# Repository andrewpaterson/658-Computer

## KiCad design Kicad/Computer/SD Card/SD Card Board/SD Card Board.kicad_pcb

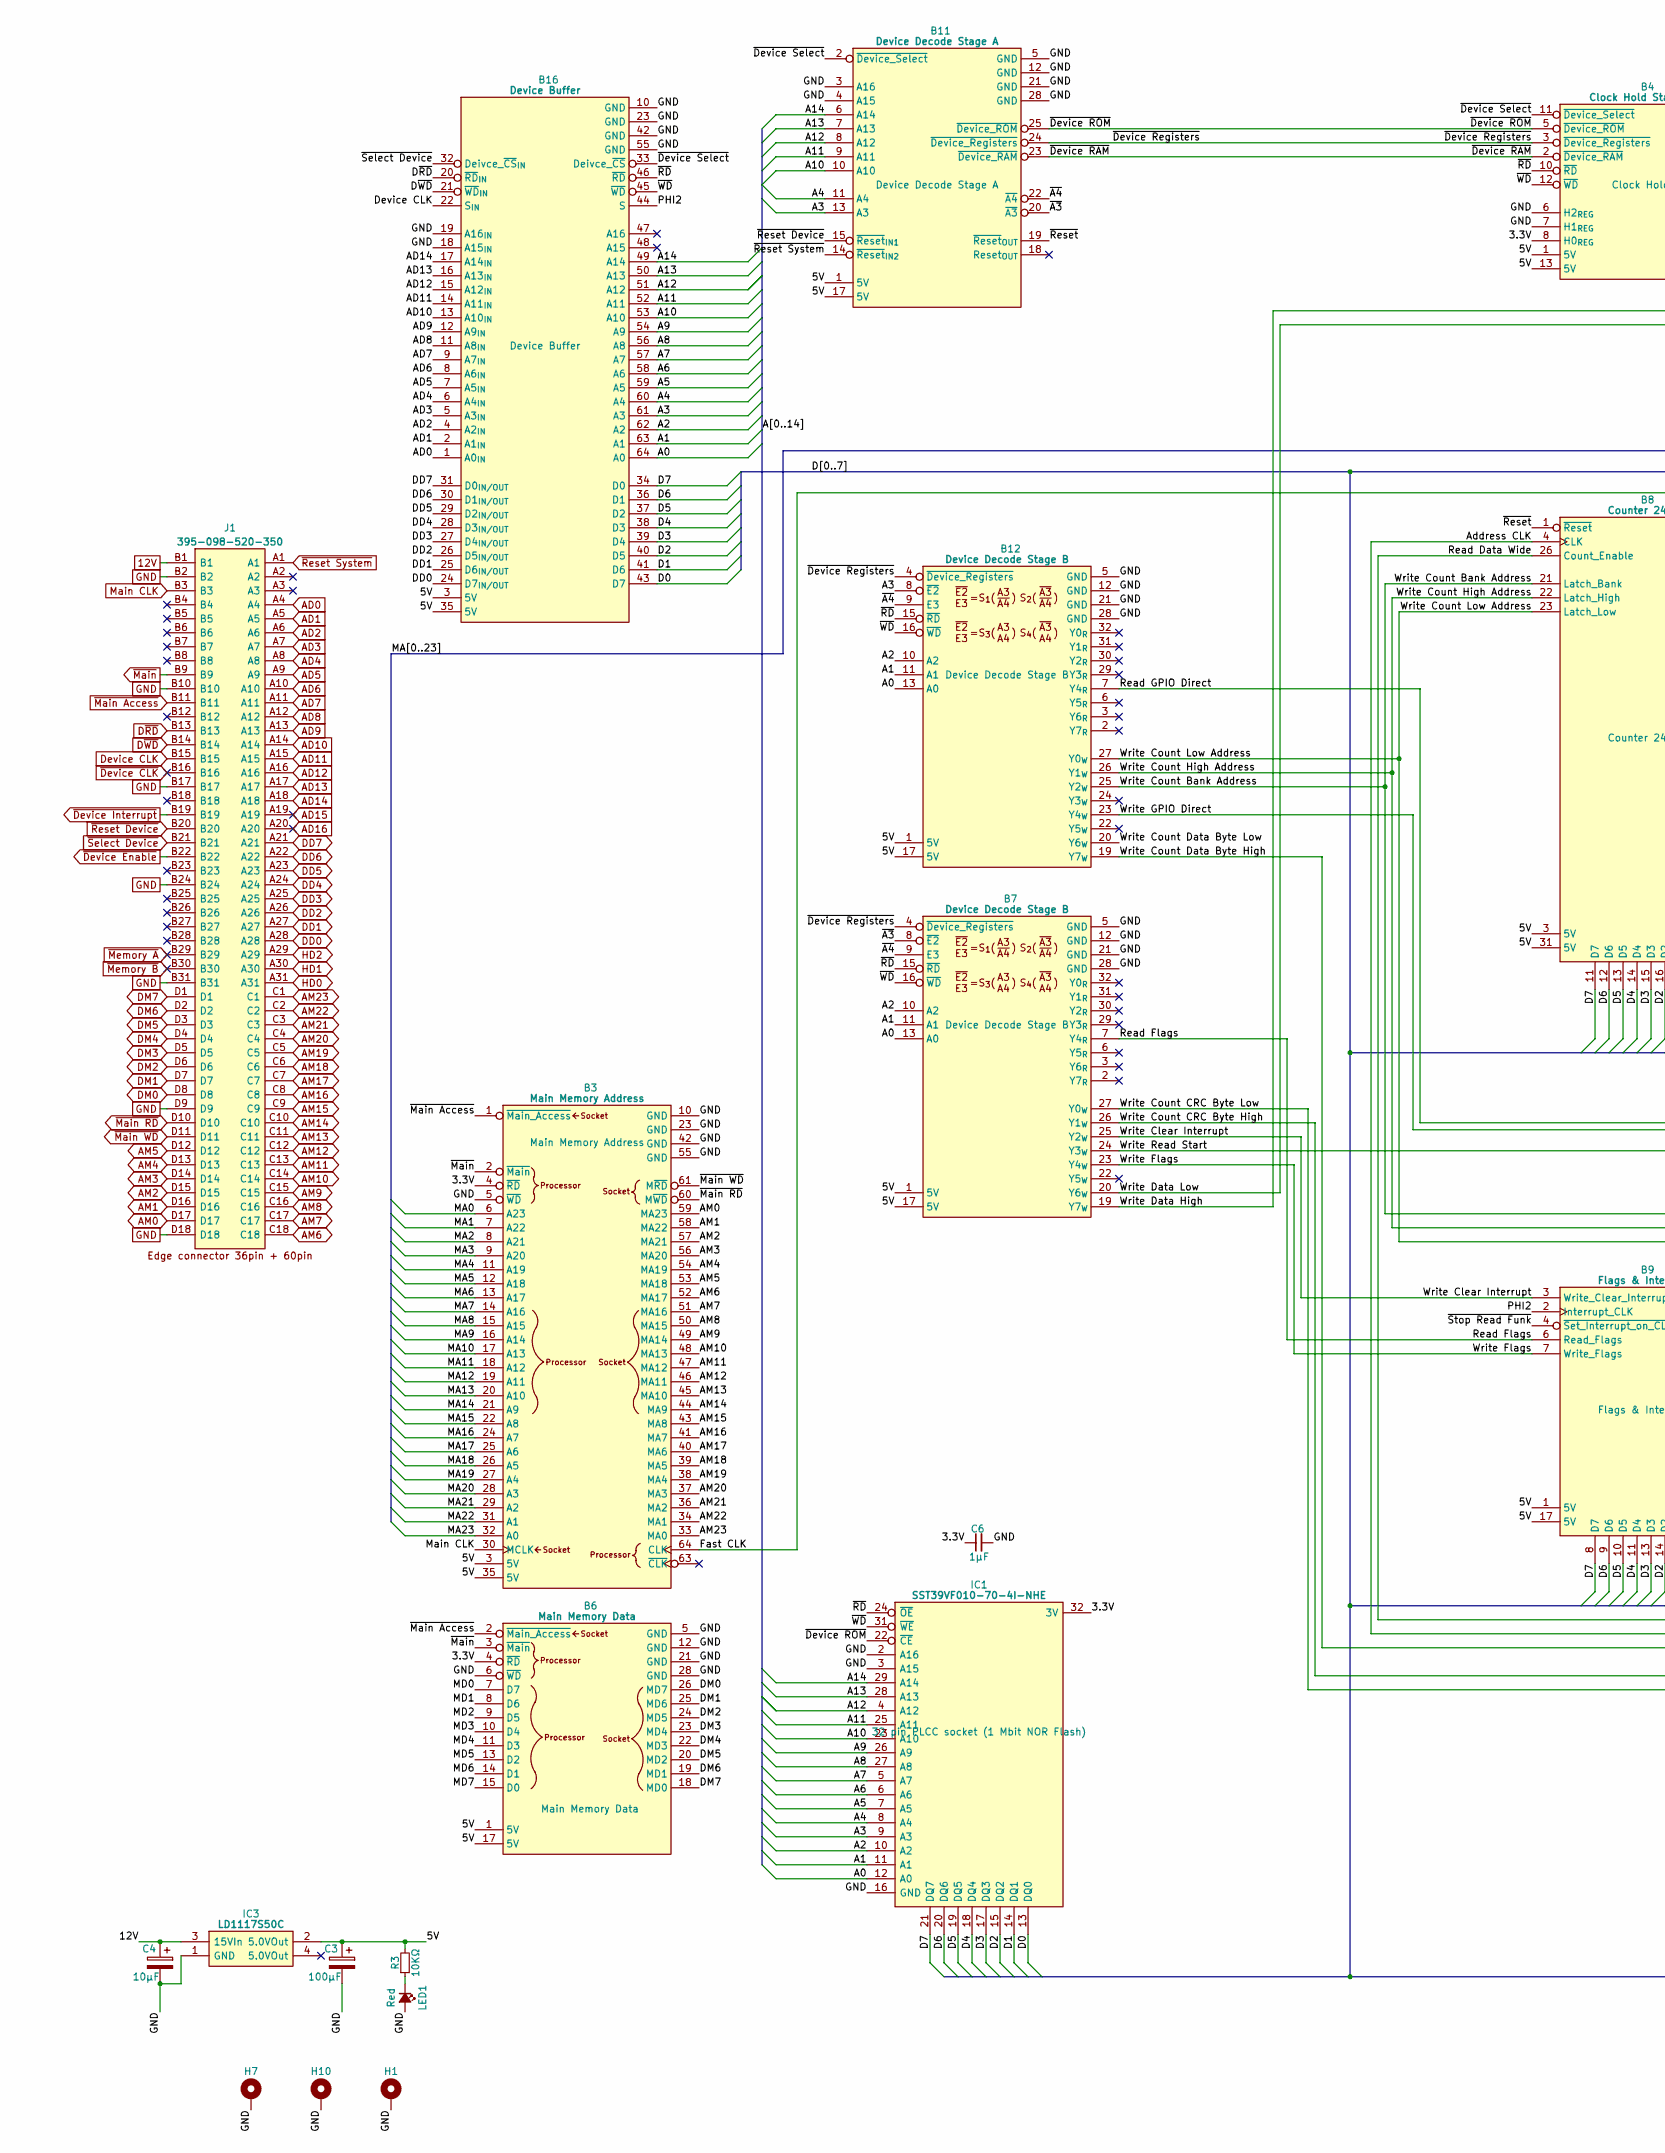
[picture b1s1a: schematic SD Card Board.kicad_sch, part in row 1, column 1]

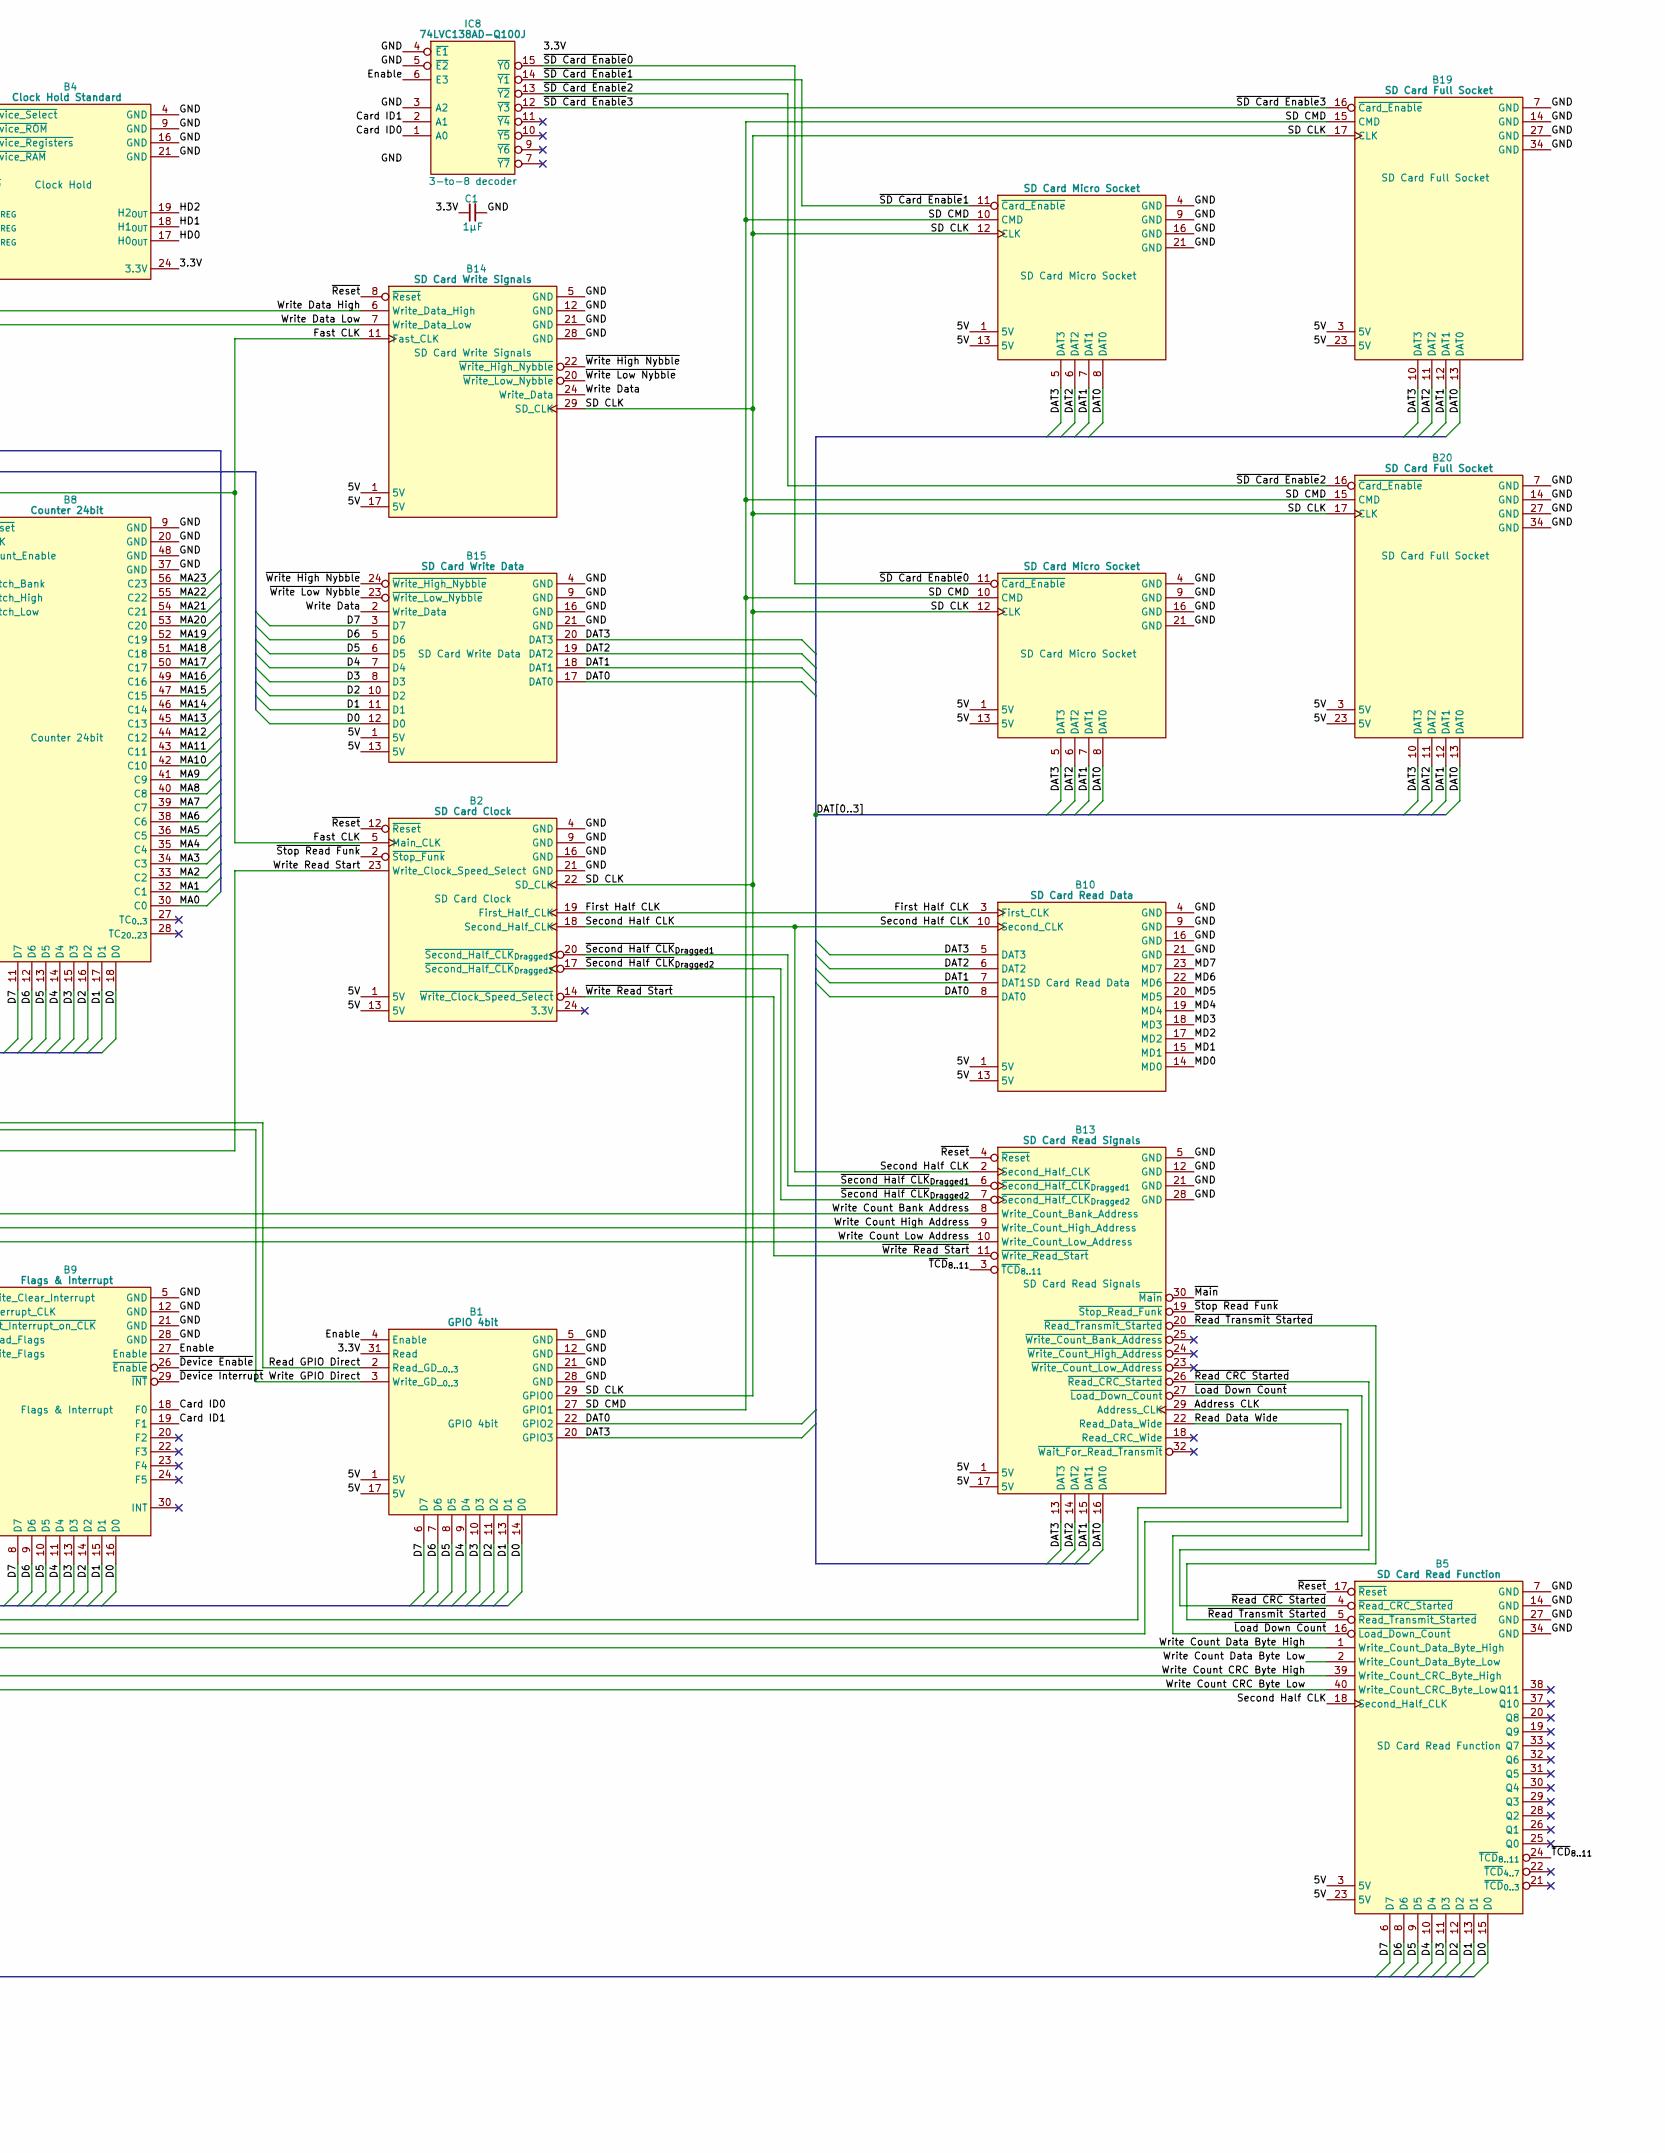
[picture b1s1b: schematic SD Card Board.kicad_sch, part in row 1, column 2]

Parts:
B1: GPIO 4bit; HCP65_GPIO_4bit
B2: SD Card Clock; HCP65_SD_Card_Clock
B3: Main Memory Address; HCP65_Main_Memory_Address
B4: Clock Hold Standard; HCP65_Clock_Hold_Standard
B5: SD Card Read Function; HCP65_SD_Card_Read_Function
B6: Main Memory Data; HCP65_Main_Memory_Data
B7, B12: Device Decode Stage B; HCP65_Device_Decode_Stage_B
B8: Counter 24bit; HCP65_Counter_24bit
B9: Flags & Interrupt; HCP65_Flags_Interrupt
B10: SD Card Read Data; HCP65_SD_Card_Read_Data
B11: Device Decode Stage A; HCP65_Device_Decode_Stage_A
B13: SD Card Read Signals; HCP65_SD_Card_Read_Signals
B14: SD Card Write Signals; HCP65_SD_Card_Write_Signals
B15: SD Card Write Data; HCP65_SD_Card_Write_Data
B16: Device Buffer; HCP65_Device_Buffer
B17, B18: SD Card Micro Socket; HCP65_SD_Card_Micro_Socket
B19, B20: SD Card Full Socket; HCP65_SD_Card_Full_Socket
C1, C6: 1μF; C_0805
C3: 100μF; CP_Radial_D4.0mm_P2.00mm
C4: 10μF; CP_Radial_D4.0mm_P2.00mm
H1, H7, H10: MountingHole_Pad; HCP65_MountingHole_M3_
IC1: SST39VF010-70-4I-NHE; 5408803224008; Manufacturer_Part_Number SST39VF010-70-4I-NHE
IC3: LD1117S50C; LD1117S33C; Manufacturer_Part_Number LD1117S50C
IC8: 74LVC138AD-Q100J; SOIC127P600X175-16N; Mouser Part Number 771-74LVC138ADQ100J
J1: 395-098-520-350; 98pin Edge Connector; Manufacturer_Part_Number 395-098-520-350; Mouser Part Number 587-395-098-520-350
LED1: Red; LED_D5.0mm
R3: 10KΩ; R_0805

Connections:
12V: C4.1, IC3.3 (15VIn), J1.B1
/3.3V: B1.31 (Read), B3.4 (~RD), B4.8 (H0_{REG}), B4.24 (3.3V), B6.4 (~RD), C1.1, C6.1, IC1.32 (3V), IC8.16 (3V)
/5V: B1.1 (5V), B1.17 (5V), B2.1 (5V), B2.13 (5V), B3.3 (5V), B3.35 (5V), B4.1 (5V), B4.13 (5V), B5.3 (5V), B5.23 (5V), B6.1 (5V), B6.17 (5V), B7.1 (5V), B7.17 (5V), B8.3 (5V), B8.31 (5V), B9.1 (5V), B9.17 (5V), B10.1 (5V), B10.13 (5V), B11.1 (5V), B11.17 (5V), B12.1 (5V), B12.17 (5V), B13.1 (5V), B13.17 (5V), B14.1 (5V), B14.17 (5V), B15.1 (5V), B15.13 (5V), B16.3 (5V), B16.35 (5V), B17.1 (5V), B17.13 (5V), B18.1 (5V), B18.13 (5V), B19.3 (5V), B19.23 (5V), B20.3 (5V), B20.23 (5V), C3.1, IC3.2 (5.0VOut), R3.2
/A0: B7.13 (A0), B12.13 (A0), B16.64 (A0), IC1.12 (A0)
/A1: B7.11 (A1), B12.11 (A1), B16.63 (A1), IC1.11 (A1)
/A2: B7.10 (A2), B12.10 (A2), B16.62 (A2), IC1.10 (A2)
/A3: B11.13 (A3), B12.8 (~E2), B16.61 (A3), IC1.9 (A3)
/A4: B11.11 (A4), B16.60 (A4), IC1.8 (A4)
/A5: B16.59 (A5), IC1.7 (A5)
/A6: B16.58 (A6), IC1.6 (A6)
/A7: B16.57 (A7), IC1.5 (A7)
/A8: B16.56 (A8), IC1.27 (A8)
/A9: B16.54 (A9), IC1.26 (A9)
/A10: B11.10 (A10), B16.53 (A10), IC1.23 (A10)
/A11: B11.9 (A11), B16.52 (A11), IC1.25 (A11)
/A12: B11.8 (A12), B16.51 (A12), IC1.4 (A12)
/A13: B11.7 (A13), B16.50 (A13), IC1.28 (A13)
/A14: B11.6 (A14), B16.49 (A14), IC1.29 (A14)
/Address CLK: B8.4 (CLK), B13.29 (Address_CLK)
/Card ID0: B9.18 (F0), IC8.1 (A0)
/Card ID1: B9.19 (F1), IC8.2 (A1)
/D0: B1.14 (D0), B5.15 (D0), B8.18 (D0), B9.16 (D0), B15.12 (D0), B16.43 (D7), IC1.13 (DQ0)
/D1: B1.13 (D1), B5.13 (D1), B8.17 (D1), B9.15 (D1), B15.11 (D1), B16.41 (D6), IC1.14 (DQ1)
/D2: B1.11 (D2), B5.12 (D2), B8.16 (D2), B9.14 (D2), B15.10 (D2), B16.40 (D5), IC1.15 (DQ2)
/D3: B1.10 (D3), B5.11 (D3), B8.15 (D3), B9.13 (D3), B15.8 (D3), B16.39 (D4), IC1.17 (DQ3)
/D4: B1.9 (D4), B5.10 (D4), B8.14 (D4), B9.11 (D4), B15.7 (D4), B16.38 (D3), IC1.18 (DQ4)
/D5: B1.8 (D5), B5.9 (D5), B8.13 (D5), B9.10 (D5), B15.6 (D5), B16.37 (D2), IC1.19 (DQ5)
/D6: B1.7 (D6), B5.8 (D6), B8.12 (D6), B9.9 (D6), B15.5 (D6), B16.36 (D1), IC1.20 (DQ6)
/D7: B1.6 (D7), B5.6 (D7), B8.11 (D7), B9.8 (D7), B15.3 (D7), B16.34 (D0), IC1.21 (DQ7)
/DAT0: B1.22 (GPIO2), B10.8 (DAT0), B13.16 (DAT0), B15.17 (DAT0), B17.8 (DAT0), B18.8 (DAT0), B19.13 (DAT0), B20.13 (DAT0)
/DAT1: B10.7 (DAT1), B13.15 (DAT1), B15.18 (DAT1), B17.7 (DAT1), B18.7 (DAT1), B19.12 (DAT1), B20.12 (DAT1)
/DAT2: B10.6 (DAT2), B13.14 (DAT2), B15.19 (DAT2), B17.6 (DAT2), B18.6 (DAT2), B19.11 (DAT2), B20.11 (DAT2)
/DAT3: B1.20 (GPIO3), B10.5 (DAT3), B13.13 (DAT3), B15.20 (DAT3), B17.5 (DAT3), B18.5 (DAT3), B19.10 (DAT3), B20.10 (DAT3)
/Enable: B1.4 (Enable), B9.27 (Enable), IC8.6 (E3)
/Fast CLK: B2.5 (Main_CLK), B3.64 (CLK), B14.11 (Fast_CLK)
/First Half CLK: B2.19 (First_Half_CLK), B10.3 (First_CLK)
/MA0: B3.6 (A23), B8.30 (C0)
/MA1: B3.7 (A22), B8.32 (C1)
/MA2: B3.8 (A21), B8.33 (C2)
/MA3: B3.9 (A20), B8.34 (C3)
/MA4: B3.11 (A19), B8.35 (C4)
/MA5: B3.12 (A18), B8.36 (C5)
/MA6: B3.13 (A17), B8.38 (C6)
/MA7: B3.14 (A16), B8.39 (C7)
/MA8: B3.15 (A15), B8.40 (C8)
/MA9: B3.16 (A14), B8.41 (C9)
/MA10: B3.17 (A13), B8.42 (C10)
/MA11: B3.18 (A12), B8.43 (C11)
/MA12: B3.19 (A11), B8.44 (C12)
/MA13: B3.20 (A10), B8.45 (C13)
/MA14: B3.21 (A9), B8.46 (C14)
/MA15: B3.22 (A8), B8.47 (C15)
/MA16: B3.24 (A7), B8.49 (C16)
/MA17: B3.25 (A6), B8.50 (C17)
/MA18: B3.26 (A5), B8.51 (C18)
/MA19: B3.27 (A4), B8.52 (C19)
/MA20: B3.28 (A3), B8.53 (C20)
/MA21: B3.29 (A2), B8.54 (C21)
/MA22: B3.31 (A1), B8.55 (C22)
/MA23: B3.32 (A0), B8.56 (C23)
/MD0: B6.7 (D7), B10.14 (MD0)
/MD1: B6.8 (D6), B10.15 (MD1)
/MD2: B6.9 (D5), B10.17 (MD2)
/MD3: B6.10 (D4), B10.18 (MD3)
/MD4: B6.11 (D3), B10.19 (MD4)
/MD5: B6.13 (D2), B10.20 (MD5)
/MD6: B6.14 (D1), B10.22 (MD6)
/MD7: B6.15 (D0), B10.23 (MD7)
/PHI2: B9.2 (Interrupt_CLK), B16.44 (S)
/Read Data Wide: B8.26 (Count_Enable), B13.22 (Read_Data_Wide)
/Read Flags: B7.7 (Y4_{R}), B9.6 (Read_Flags)
/Read GPIO Direct: B1.2 (Read_GD__{0..3}), B12.7 (Y4_{R})
/SD CLK: B1.29 (GPIO0), B2.22 (SD_CLK), B14.29 (SD_CLK), B17.12 (CLK), B18.12 (CLK), B19.17 (CLK), B20.17 (CLK)
/SD CMD: B1.27 (GPIO1), B17.10 (CMD), B18.10 (CMD), B19.15 (CMD), B20.15 (CMD)
/Second Half CLK: B2.18 (Second_Half_CLK), B5.18 (Second_Half_CLK), B10.10 (Second_CLK), B13.2 (Second_Half_CLK)
/Write Clear Interrupt: B7.25 (Y2_{W}), B9.3 (Write_Clear_Interrupt)
/Write Count Bank Address: B8.21 (Latch_Bank), B12.25 (Y2_{W}), B13.8 (Write_Count_Bank_Address)
/Write Count CRC Byte High: B5.39 (Write_Count_CRC_Byte_High), B7.26 (Y1_{W})
/Write Count CRC Byte Low: B5.40 (Write_Count_CRC_Byte_Low), B7.27 (Y0_{W})
/Write Count Data Byte High: B5.1 (Write_Count_Data_Byte_High), B12.19 (Y7_{W})
/Write Count Data Byte Low: B5.2 (Write_Count_Data_Byte_Low), B12.20 (Y6_{W})
/Write Count High Address: B8.22 (Latch_High), B12.26 (Y1_{W}), B13.9 (Write_Count_High_Address)
/Write Count Low Address: B8.23 (Latch_Low), B12.27 (Y0_{W}), B13.10 (Write_Count_Low_Address)
/Write Data: B14.24 (Write_Data), B15.2 (Write_Data)
/Write Data High: B7.19 (Y7_{W}), B14.6 (Write_Data_High)
/Write Data Low: B7.20 (Y6_{W}), B14.7 (Write_Data_Low)
/Write Flags: B7.23 (Y4_{W}), B9.7 (Write_Flags)
/Write GPIO Direct: B1.3 (Write_GD__{0..3}), B12.23 (Y4_{W})
/Write Read Start: B2.23 (Write_Clock_Speed_Select), B7.24 (Y3_{W})
/~A3: B7.8 (~E2), B11.20 (~A3)
/~A4: B7.9 (E3), B11.22 (~A4), B12.9 (E3)
/~Device RAM: B4.2 (~Device_RAM), B11.23 (~Device_RAM)
/~Device ROM: B4.5 (~Device_ROM), B11.25 (~Device_ROM), IC1.22 (~CE)
/~Device Registers: B4.3 (~Device_Registers), B7.4 (~Device_Registers), B11.24 (~Device_Registers), B12.4 (~Device_Registers)
/~Device Select: B4.11 (~Device_Select), B11.2 (~Device_Select), B16.33 (Deivce_~CS)
/~Load Down Count: B5.16 (~Load_Down_Count), B13.27 (~Load_Down_Count)
/~RD: B4.10 (~RD), B7.15 (~RD), B12.15 (~RD), B16.46 (~RD), IC1.24 (~OE)
/~Read CRC Started: B5.4 (~Read_CRC_Started), B13.26 (~Read_CRC_Started)
/~Read Transmit Started: B5.5 (~Read_Transmit_Started), B13.20 (~Read_Transmit_Started)
/~Reset: B2.12 (~Reset), B5.17 (~Reset), B8.1 (~Reset), B11.19 (~Reset_{OUT}), B13.4 (~Reset), B14.8 (~Reset)
/~SD Card Enable0: B17.11 (~Card_Enable), IC8.15 (~Y0)
/~SD Card Enable1: B18.11 (~Card_Enable), IC8.14 (~Y1)
/~SD Card Enable2: B20.16 (~Card_Enable), IC8.13 (~Y2)
/~SD Card Enable3: B19.16 (~Card_Enable), IC8.12 (~Y3)
/~Second Half CLK_{Dragged1}: B2.20 (~Second_Half_CLK_{Dragged1}), B13.6 (~Second_Half_CLK_{Dragged1})
/~Second Half CLK_{Dragged2}: B2.17 (~Second_Half_CLK_{Dragged2}), B13.7 (~Second_Half_CLK_{Dragged2})
/~Stop Read Funk: B2.2 (~Stop_Funk), B9.4 (~Set_Interrupt_on_CLK), B13.19 (~Stop_Read_Funk)
/~TCD_{8..11}: B5.24 (~TCD_{8..11}), B13.3 (~TCD_{8..11})
/~WD: B4.12 (~WD), B7.16 (~WD), B12.16 (~WD), B16.45 (~WD), IC1.31 (~WE)
/~Write High Nybble: B14.22 (~Write_High_Nybble), B15.24 (~Write_High_Nybble)
/~Write Low Nybble: B14.20 (~Write_Low_Nybble), B15.23 (~Write_Low_Nybble)
/~Write Read Start: B2.14 (~Write_Clock_Speed_Select), B13.11 (~Write_Read_Start)
AD0: B16.1 (A0_{IN}), J1.A4
AD1: B16.2 (A1_{IN}), J1.A5
AD2: B16.4 (A2_{IN}), J1.A6
AD3: B16.5 (A3_{IN}), J1.A7
AD4: B16.6 (A4_{IN}), J1.A8
AD5: B16.7 (A5_{IN}), J1.A9
AD6: B16.8 (A6_{IN}), J1.A10
AD7: B16.9 (A7_{IN}), J1.A11
AD8: B16.11 (A8_{IN}), J1.A12
AD9: B16.12 (A9_{IN}), J1.A13
AD10: B16.13 (A10_{IN}), J1.A14
AD11: B16.14 (A11_{IN}), J1.A15
AD12: B16.15 (A12_{IN}), J1.A16
AD13: B16.16 (A13_{IN}), J1.A17
AD14: B16.17 (A14_{IN}), J1.A18
AD15: J1.A19
AD16: J1.A20
AM0: B3.59 (MA23), J1.D17
AM1: B3.58 (MA22), J1.D16
AM2: B3.57 (MA21), J1.D15
AM3: B3.56 (MA20), J1.D14
AM4: B3.54 (MA19), J1.D13
AM5: B3.53 (MA18), J1.D12
AM6: B3.52 (MA17), J1.C18
AM7: B3.51 (MA16), J1.C17
AM8: B3.50 (MA15), J1.C16
AM9: B3.49 (MA14), J1.C15
AM10: B3.48 (MA13), J1.C14
AM11: B3.47 (MA12), J1.C13
AM12: B3.46 (MA11), J1.C12
AM13: B3.45 (MA10), J1.C11
AM14: B3.44 (MA9), J1.C10
AM15: B3.43 (MA8), J1.C9
AM16: B3.41 (MA7), J1.C8
AM17: B3.40 (MA6), J1.C7
AM18: B3.39 (MA5), J1.C6
AM19: B3.38 (MA4), J1.C5
AM20: B3.37 (MA3), J1.C4
AM21: B3.36 (MA2), J1.C3
AM22: B3.34 (MA1), J1.C2
AM23: B3.33 (MA0), J1.C1
DD0: B16.24 (D7_{IN/OUT}), J1.A28
DD1: B16.25 (D6_{IN/OUT}), J1.A27
DD2: B16.26 (D5_{IN/OUT}), J1.A26
DD3: B16.27 (D4_{IN/OUT}), J1.A25
DD4: B16.28 (D3_{IN/OUT}), J1.A24
DD5: B16.29 (D2_{IN/OUT}), J1.A23
DD6: B16.30 (D1_{IN/OUT}), J1.A22
DD7: B16.31 (D0_{IN/OUT}), J1.A21
DM0: B6.26 (MD7), J1.D8
DM1: B6.25 (MD6), J1.D7
DM2: B6.24 (MD5), J1.D6
DM3: B6.23 (MD4), J1.D5
DM4: B6.22 (MD3), J1.D4
DM5: B6.20 (MD2), J1.D3
DM6: B6.19 (MD1), J1.D2
DM7: B6.18 (MD0), J1.D1
Device CLK: B16.22 (S_{IN}), J1.B15
D~RD: B16.20 (~RD_{IN}), J1.B13
D~WD: B16.21 (~WD_{IN}), J1.B14
GND: B1.5 (GND), B1.12 (GND), B1.21 (GND), B1.28 (GND), B2.4 (GND), B2.9 (GND), B2.16 (GND), B2.21 (GND), B3.5 (~WD), B3.10 (GND), B3.23 (GND), B3.42 (GND), B3.55 (GND), B4.4 (GND), B4.6 (H2_{REG}), B4.7 (H1_{REG}), B4.9 (GND), B4.16 (GND), B4.21 (GND), B5.7 (GND), B5.14 (GND), B5.27 (GND), B5.34 (GND), B6.5 (GND), B6.6 (~WD), B6.12 (GND), B6.21 (GND), B6.28 (GND), B7.5 (GND), B7.12 (GND), B7.21 (GND), B7.28 (GND), B8.9 (GND), B8.20 (GND), B8.37 (GND), B8.48 (GND), B9.5 (GND), B9.12 (GND), B9.21 (GND), B9.28 (GND), B10.4 (GND), B10.9 (GND), B10.16 (GND), B10.21 (GND), B11.3 (A16), B11.4 (A15), B11.5 (GND), B11.12 (GND), B11.21 (GND), B11.28 (GND), B12.5 (GND), B12.12 (GND), B12.21 (GND), B12.28 (GND), B13.5 (GND), B13.12 (GND), B13.21 (GND), B13.28 (GND), B14.5 (GND), B14.12 (GND), B14.21 (GND), B14.28 (GND), B15.4 (GND), B15.9 (GND), B15.16 (GND), B15.21 (GND), B16.10 (GND), B16.18 (A15_{IN}), B16.19 (A16_{IN}), B16.23 (GND), B16.42 (GND), B16.55 (GND), B17.4 (GND), B17.9 (GND), B17.16 (GND), B17.21 (GND), B18.4 (GND), B18.9 (GND), B18.16 (GND), B18.21 (GND), B19.7 (GND), B19.14 (GND), B19.27 (GND), B19.34 (GND), B20.7 (GND), B20.14 (GND), B20.27 (GND), B20.34 (GND), C1.2, C3.2, C4.2, C6.2, H1.1 (GND), H7.1 (GND), H10.1 (GND), IC1.2 (A16), IC1.3 (A15), IC1.16 (GND), IC3.1 (GND), IC8.3 (A2), IC8.4 (~E1), IC8.5 (~E2), IC8.8 (GND), J1.B2, J1.B10, J1.B17, J1.B24, J1.B31, J1.D9, J1.D18, LED1.2 (A)
HD0: B4.17 (H0_{OUT}), J1.A31
HD1: B4.18 (H1_{OUT}), J1.A30
HD2: B4.19 (H2_{OUT}), J1.A29
Main CLK: B3.30 (MCLK), J1.B3
unnamed: LED1.1 (K), R3.1
~Device CLK: J1.B16
~Device Enable: B9.26 (~Enable), J1.B22
~Device Interrupt: B9.29 (~INT), J1.B19
~Main Access: B3.1 (~Main_Access), B6.2 (~Main_Access), J1.B11
~Main RD: B3.60 (M~WD), J1.D10
~Main WD: B3.61 (M~RD), J1.D11
~Main: B3.2 (~Main), B6.3 (~Main), B13.30 (~Main), J1.B9
~Memory A: J1.B29
~Memory B: J1.B30
~Reset Device: B11.15 (~Reset_{IN1}), J1.B20
~Reset System: B11.14 (~Reset_{IN2}), J1.A1
~Select Device: B16.32 (Deivce_~CS_{IN}), J1.B21

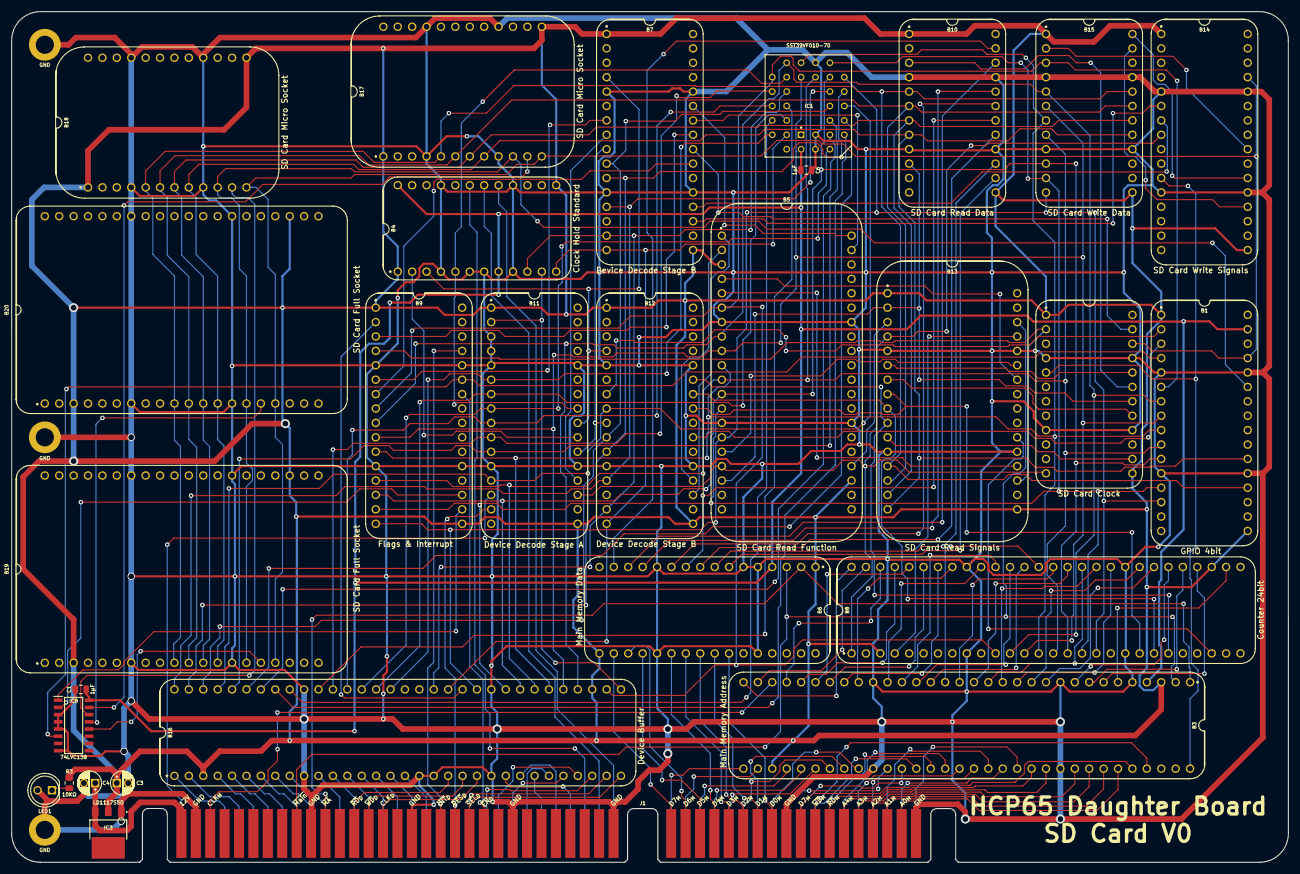
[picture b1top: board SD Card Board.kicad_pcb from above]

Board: 2 copper layers, 225.1 x 150.0 mm, 33 parts (0 on the bottom side), 185 nets.

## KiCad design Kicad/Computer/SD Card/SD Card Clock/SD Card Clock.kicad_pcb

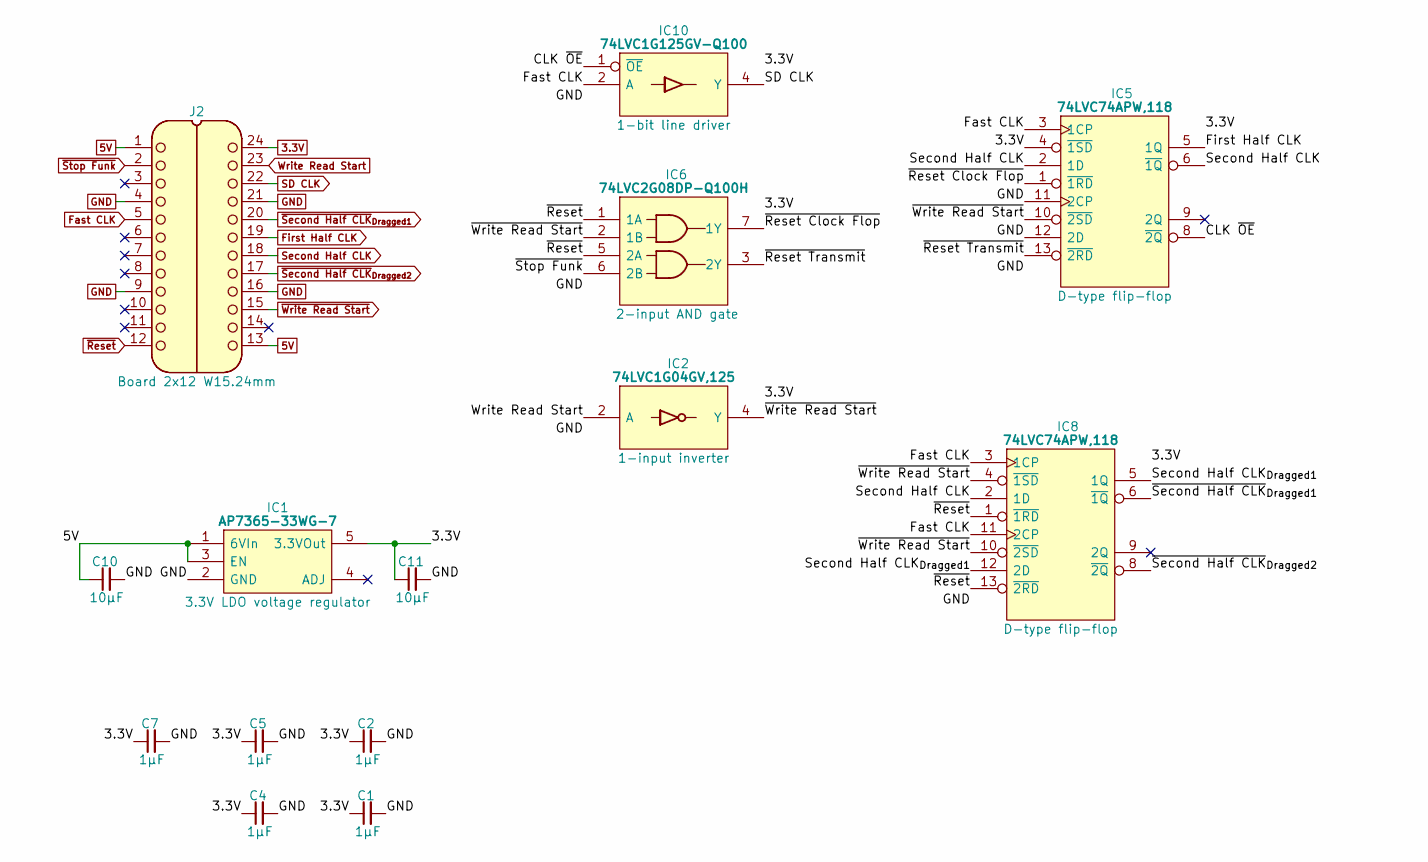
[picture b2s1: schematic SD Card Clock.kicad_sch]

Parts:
C1, C2, C4, C5, C7: 1μF; C_0805
C10, C11: 10µF; C_0805
IC1: AP7365-33WG-7; SOT95P285X130-5N; Manufacturer_Part_Number AP7365-33WG-7; Mouser Part Number 621-AP7365-33WG-7
IC2: 74LVC1G04GV,125; SOT95P275X110-5N; Manufacturer_Part_Number 74LVC1G04GV,125; Mouser Part Number 771-74LVC1G04GV
IC5, IC8: 74LVC74APW,118; SOP65P640X110-14N; Mouser Part Number 771-74LVC74APW-T
IC6: 74LVC2G08DP-Q100H; SOP65P400X110-8N; Manufacturer_Part_Number 74LVC2G08DP-Q100H; Mouser Part Number 771-74LVC2G08DPQ100H
IC10: 74LVC1G125GV-Q100; SOT95P275X110-5N; Mouser Part Number 771-74LVC1G125GVQ100
J2: Board 2x12 W15.24mm; DIP-24_Board_W15.24mm

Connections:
3.3V: C1.1, C2.1, C4.1, C5.1, C7.1, C11.1, IC1.5 (3.3VOut), IC2.5 (3V), IC5.4 (~1SD), IC5.14 (3V), IC6.8 (3V), IC8.14 (3V), IC10.5 (3V), J2.24
5V: C10.1, IC1.1 (6VIn), IC1.3 (EN), J2.1, J2.13
/CLK ~OE: IC5.8 (~2Q), IC10.1 (~OE)
/Second Half CLK_{Dragged1}: IC8.5 (1Q), IC8.12 (2D)
/~Reset Clock Flop: IC5.1 (~1RD), IC6.7 (1Y)
/~Reset Transmit: IC5.13 (~2RD), IC6.3 (2Y)
Fast CLK: IC5.3 (1CP), IC8.3 (1CP), IC8.11 (2CP), IC10.2 (A), J2.5
First Half CLK: IC5.5 (1Q), J2.19
GND: C1.2, C2.2, C4.2, C5.2, C7.2, C10.2, C11.2, IC1.2 (GND), IC2.3 (GND), IC5.7 (GND), IC5.11 (2CP), IC5.12 (2D), IC6.4 (GND), IC8.7 (GND), IC10.3 (GND), J2.4, J2.9, J2.16, J2.21
SD CLK: IC10.4 (Y), J2.22
Second Half CLK: IC5.2 (1D), IC5.6 (~1Q), IC8.2 (1D), J2.18
Write Read Start: IC2.2 (A), J2.23
~Reset: IC6.1 (1A), IC6.5 (2A), IC8.1 (~1RD), IC8.13 (~2RD), J2.12
~Second Half CLK_{Dragged1}: IC8.6 (~1Q), J2.20
~Second Half CLK_{Dragged2}: IC8.8 (~2Q), J2.17
~Stop Funk: IC6.6 (2B), J2.2
~Write Read Start: IC2.4 (Y), IC5.10 (~2SD), IC6.2 (1B), IC8.4 (~1SD), IC8.10 (~2SD), J2.15

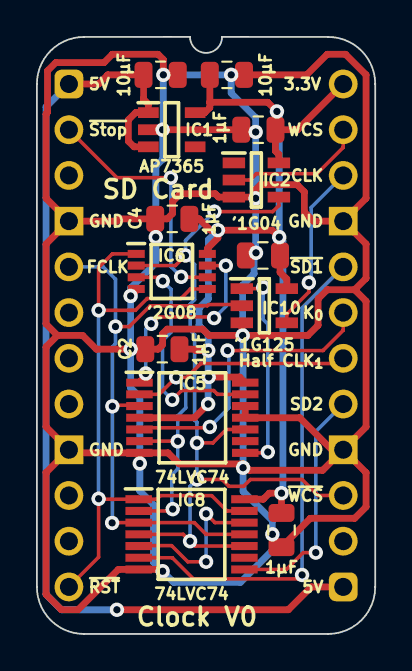
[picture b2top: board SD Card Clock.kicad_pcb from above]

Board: 2 copper layers, 18.8 x 33.2 mm, 14 parts (0 on the bottom side), 17 nets.

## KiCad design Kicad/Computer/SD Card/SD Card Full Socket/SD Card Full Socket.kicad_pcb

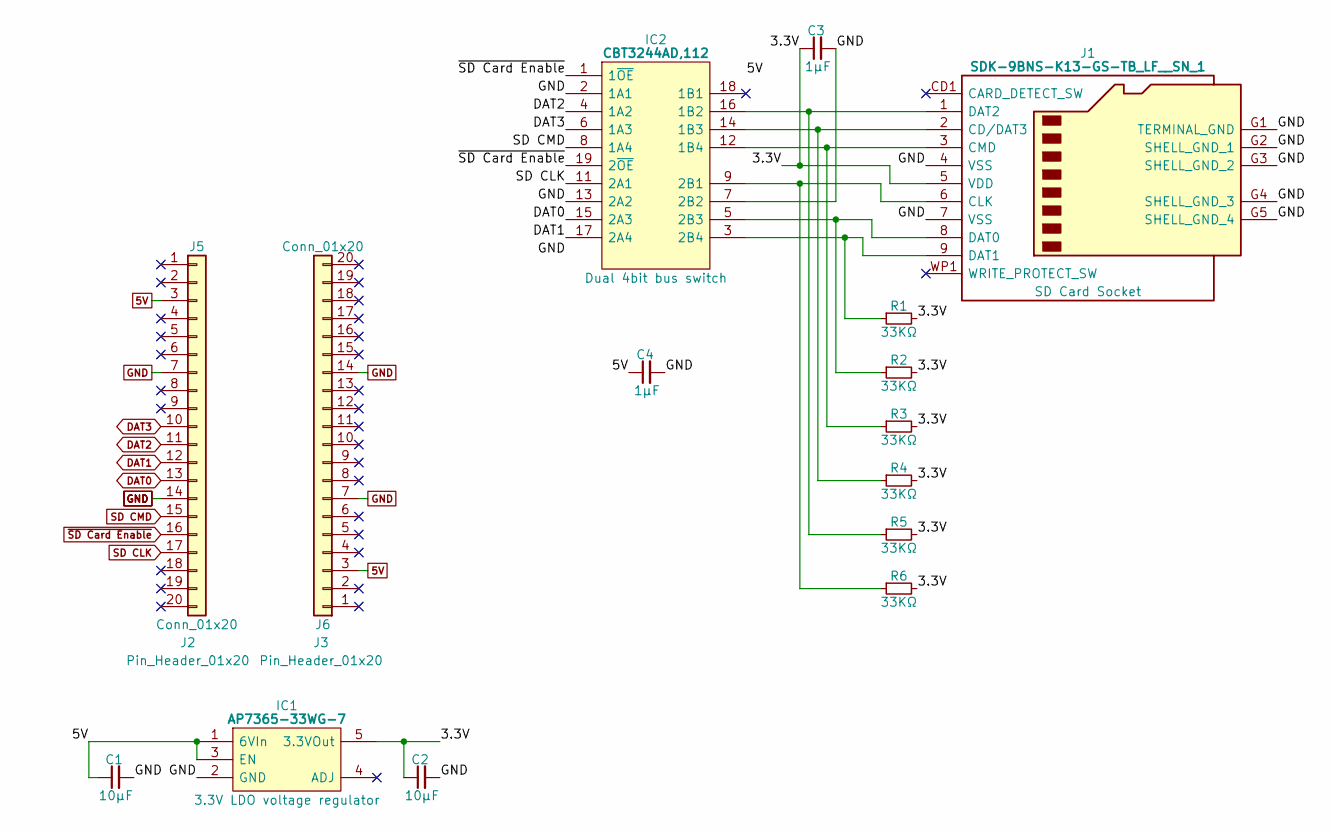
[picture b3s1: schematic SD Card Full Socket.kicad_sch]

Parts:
C1, C2: 10μF; C_0805
C3, C4: 1μF; C_0805
IC1: AP7365-33WG-7; SOT95P285X130-5N; Manufacturer_Part_Number AP7365-33WG-7; Mouser Part Number 621-AP7365-33WG-7
IC2: CBT3244AD,112; SOIC127P1032X265-20N; Manufacturer_Part_Number CBT3244AD,112; Mouser Part Number 771-CBT3244AD
J1: SDK-9BNS-K13-GS-TB_LF__SN_1; SDK9BNSK13GSTBLFSN1; Manufacturer_Part_Number SDK-9BNS-K13-GS-TB(LF)(SN)1
J2, J3: Pin_Header_01x20; PinHeader_1x20_P2.54mm_Vertical
J5, J6: Conn_01x20; SIP_20_Pins
R1, R2, R3, R4, R5, R6: 33KΩ; R_0805

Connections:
5V: C1.1, C4.1, IC1.1 (6VIn), IC1.3 (EN), IC2.20 (5V), J5.3, J6.3
/3.3V: C2.1, C3.1, IC1.5 (3.3VOut), J1.5 (VDD), R1.2, R2.2, R3.2, R4.2, R5.2, R6.2
DAT0: IC2.15 (2A3), J5.13
DAT1: IC2.17 (2A4), J5.12
DAT2: IC2.4 (1A2), J5.11
DAT3: IC2.6 (1A3), J5.10
GND: C1.2, C2.2, C3.2, C4.2, IC1.2 (GND), IC2.2 (1A1), IC2.7 (2B2), IC2.10 (GND), IC2.13 (2A2), J1.4 (VSS), J1.7 (VSS), J1.G1 (TERMINAL_GND), J1.G2 (SHELL_GND_1), J1.G3 (SHELL_GND_2), J1.G4 (SHELL_GND_3), J1.G5 (SHELL_GND_4), J5.7, J5.14, J6.7, J6.14
unnamed: IC2.16 (1B2), J1.1 (DAT2), R5.1
unnamed: IC2.14 (1B3), J1.2 (CD/DAT3), R4.1
unnamed: IC2.12 (1B4), J1.3 (CMD), R3.1
unnamed: IC2.9 (2B1), J1.6 (CLK), R6.1
unnamed: IC2.5 (2B3), J1.8 (DAT0), R2.1
unnamed: IC2.3 (2B4), J1.9 (DAT1), R1.1
SD CLK: IC2.11 (2A1), J5.17
SD CMD: IC2.8 (1A4), J5.15
~SD Card Enable: IC2.1 (1~OE), IC2.19 (2~OE), J5.16

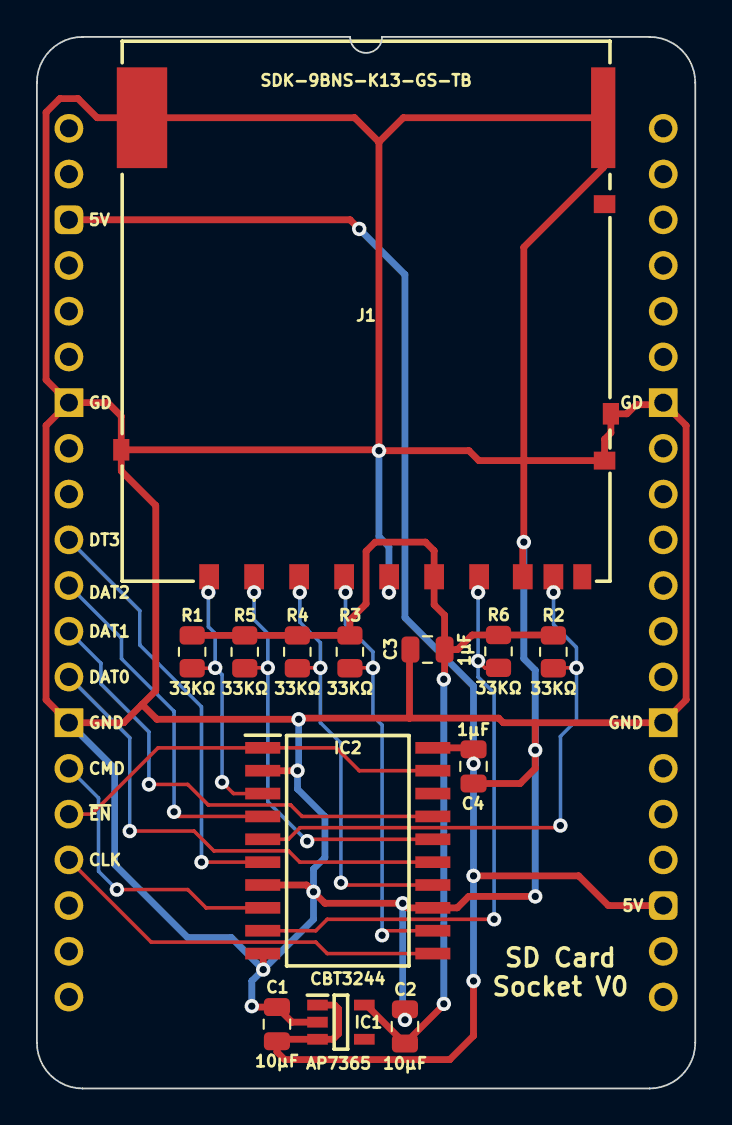
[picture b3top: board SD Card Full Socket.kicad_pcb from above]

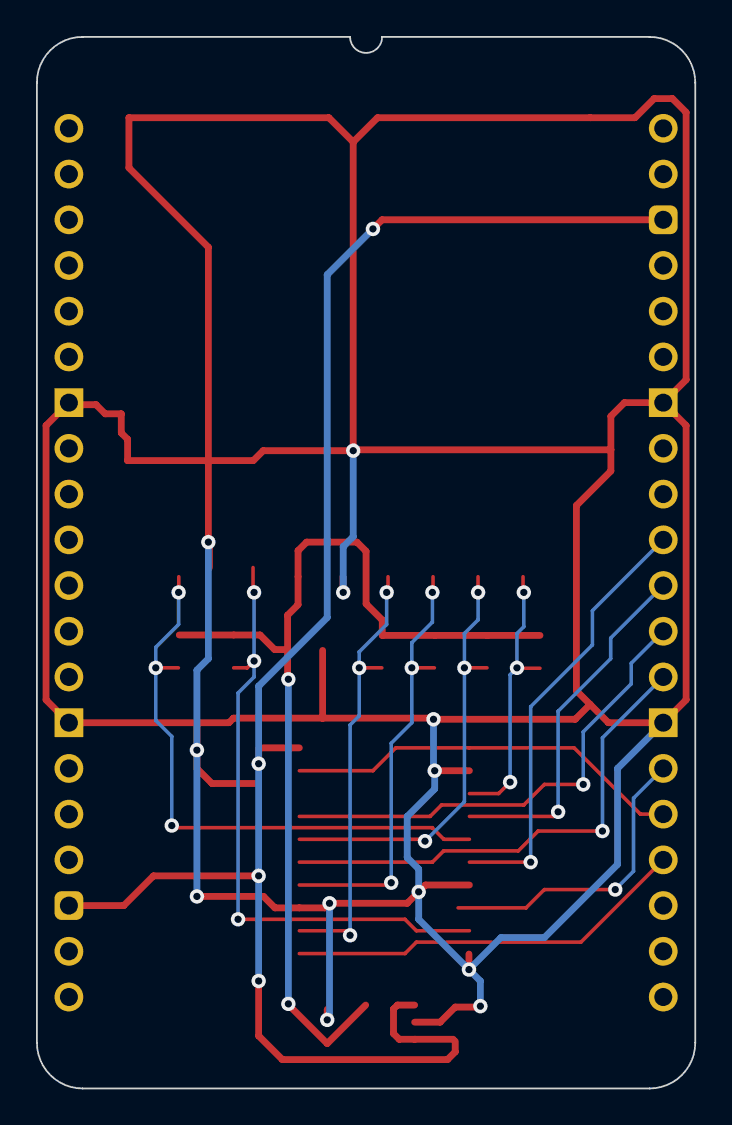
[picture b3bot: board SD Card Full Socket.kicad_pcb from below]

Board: 2 copper layers, 36.6 x 58.4 mm, 17 parts (2 on the bottom side), 16 nets.
